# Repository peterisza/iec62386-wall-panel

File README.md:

This is a smart-home wall panel that is intended to be DALI-compatible when it's finished. It has sensors for temperature, humidity, air pressure, and CO2. Its front is customizable and user-swappable with up to 16 capacitive touch channels.

## Status / Important Notice

This project is a **prototype** and **not a consumer product**. It is under active development and may be incomplete, unstable, or non-compliant with relevant standards.

### DO NOT CONNECT TO A REAL DALI NETWORK (YET)

**Do not connect this device to any production / real DALI installation.**  
The current firmware is not DALI-compliant and is intended for development only. In its current state it will:
- transmit debug frames (e.g., 16-bit debug frames),
- respond incorrectly to forward frames (e.g., fixed/placeholder back frame behavior),
- cause unexpected bus behavior.

## Safety / Disclaimer

- Provided **AS IS**, **WITHOUT WARRANTY** of any kind (express or implied).
- You are solely responsible for verifying **electrical safety**, **EMC**, and **regulatory compliance** before any real-world installation or use.
- Not intended for **safety-critical** or life-safety applications (medical, fire protection, emergency systems, etc.).
- If you 3D-print the enclosure, use appropriate **flame-retardant** materials and follow local building and electrical codes.
- By using, building, or distributing this project (or derivatives), you accept that you do so **at your own risk**.

## DALI Compatibility, Certification, and Trademarks

This project is designed with future DALI compatibility in mind, but it is **NOT DALI certified**.

- Certification is performed by the **DALI Alliance / DiiA**. This project is **not certified** and **not affiliated** with the DALI Alliance / DiiA.
- “DALI” and related marks are trademarks of their respective owners. Any mention is for compatibility and informational purposes only.

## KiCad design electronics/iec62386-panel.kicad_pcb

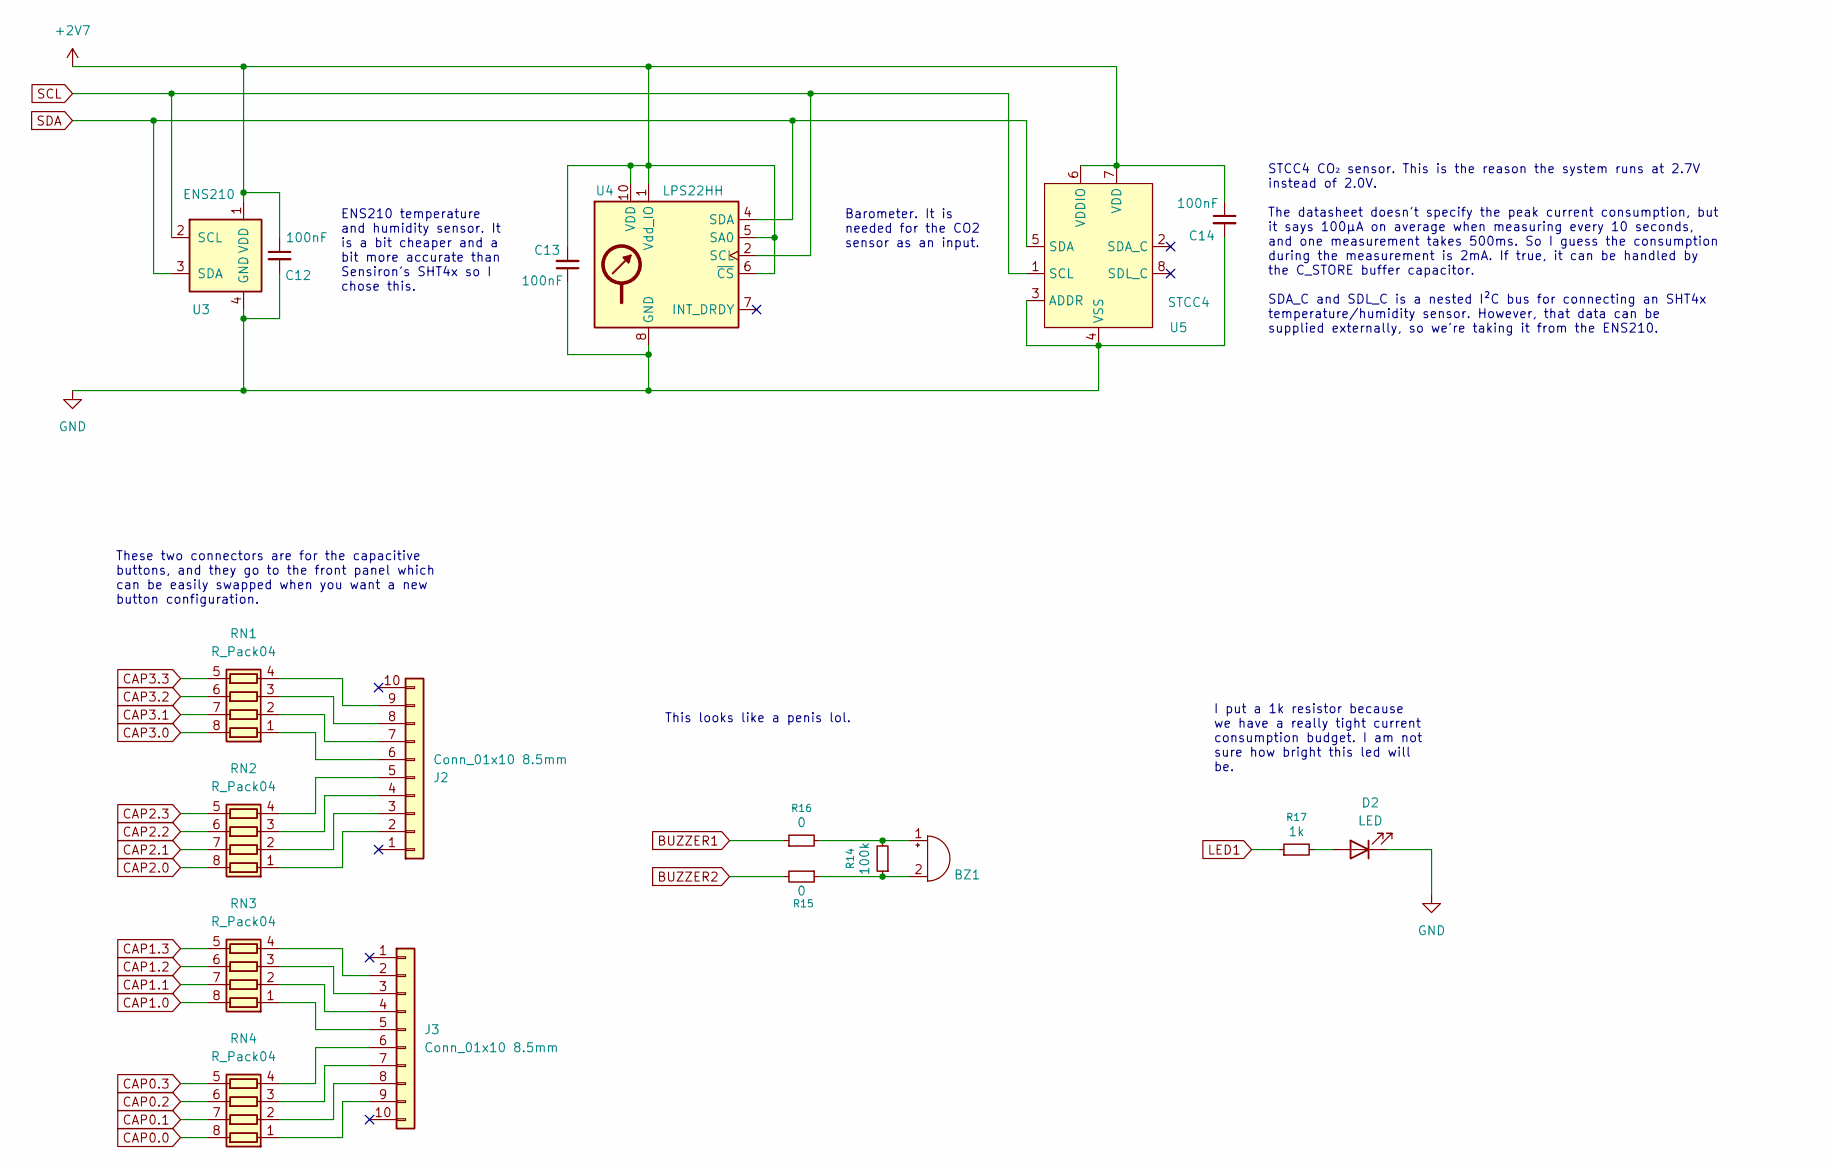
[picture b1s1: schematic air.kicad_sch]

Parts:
BZ1: Buzzer_CUI_CPT-9019S-SMT
C12, C13, C14: 100nF; C_0603_1608Metric_Pad1.08x0.95mm_HandSolder
D2: LED; LED_0603_1608Metric_Pad1.05x0.95mm_HandSolder
J2, J3: Conn_01x10 8.5mm; PinSocket_1x10_P2.54mm_Vertical
R14: 100k; R_0603_1608Metric_Pad0.98x0.95mm_HandSolder
R15, R16: 0; R_0603_1608Metric_Pad0.98x0.95mm_HandSolder
R17: 1k; R_0603_1608Metric_Pad0.98x0.95mm_HandSolder
RN1, RN2, RN3, RN4: R_Pack04; R_Cat16-4-DEBUG
U3: ENS210; AMS_QFN-4-1EP_2x2mm_P0.95mm_EP0.7x1.6mm-DEBUG
U4: LPS22HH; ST_HLGA-10_2x2mm_P0.5mm_LayoutBorder3x2y-DEBUG
U5: STCC4; STCC4-LGA

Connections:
+2V7: C12.1, C13.2, C14.1, U3.1 (VDD), U4.1 (Vdd_IO), U4.5 (SA0), U4.6 (~CS), U4.10 (VDD), U5.6 (VDDIO), U5.7 (VDD); also elsewhere on the board
BUZZER1: R16.1; also elsewhere on the board
BUZZER2: R15.2; also elsewhere on the board
CAP0.0: RN4.8 (R1.2); also elsewhere on the board
CAP0.1: RN4.7 (R2.2); also elsewhere on the board
CAP0.2: RN4.6 (R3.2); also elsewhere on the board
CAP0.3: RN4.5 (R4.2); also elsewhere on the board
CAP1.0: RN3.8 (R1.2); also elsewhere on the board
CAP1.1: RN3.7 (R2.2); also elsewhere on the board
CAP1.2: RN3.6 (R3.2); also elsewhere on the board
CAP1.3: RN3.5 (R4.2); also elsewhere on the board
CAP2.0: RN2.8 (R1.2); also elsewhere on the board
CAP2.1: RN2.7 (R2.2); also elsewhere on the board
CAP2.2: RN2.6 (R3.2); also elsewhere on the board
CAP2.3: RN2.5 (R4.2); also elsewhere on the board
CAP3.0: RN1.8 (R1.2); also elsewhere on the board
CAP3.1: RN1.7 (R2.2); also elsewhere on the board
CAP3.2: RN1.6 (R3.2); also elsewhere on the board
CAP3.3: RN1.5 (R4.2); also elsewhere on the board
GND: C12.2, C13.1, C14.2, D2.1 (K), U3.4 (GND), U3.5 (GND), U4.3 (GND), U4.8 (GND), U4.9 (GND), U5.3 (ADDR), U5.4 (VSS); also elsewhere on the board
LED1: R17.1; also elsewhere on the board
unnamed: BZ1.1 (+), R14.2, R16.2
unnamed: BZ1.2 (-), R14.1, R15.1
unnamed: D2.2 (A), R17.2
unnamed: J2.2, RN2.1 (R1.1)
unnamed: J2.3, RN2.2 (R2.1)
unnamed: J2.4, RN2.3 (R3.1)
unnamed: J2.5, RN2.4 (R4.1)
unnamed: J2.6, RN1.1 (R1.1)
unnamed: J2.7, RN1.2 (R2.1)
unnamed: J2.8, RN1.3 (R3.1)
unnamed: J2.9, RN1.4 (R4.1)
unnamed: J3.2, RN3.4 (R4.1)
unnamed: J3.3, RN3.3 (R3.1)
unnamed: J3.4, RN3.2 (R2.1)
unnamed: J3.5, RN3.1 (R1.1)
unnamed: J3.6, RN4.4 (R4.1)
unnamed: J3.7, RN4.3 (R3.1)
unnamed: J3.8, RN4.2 (R2.1)
unnamed: J3.9, RN4.1 (R1.1)
SCL: U3.2 (SCL), U4.2 (SCL), U5.1 (SCL); also elsewhere on the board
SDA: U3.3 (SDA), U4.4 (SDA), U5.5 (SDA); also elsewhere on the board

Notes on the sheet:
Barometer. It is needed for the CO2 sensor as an input.
STCC4 CO₂ sensor. This is the reason the system runs at 2.7V instead of 2.0V. The datasheet doesn't specify the peak current consumption, but it says 100µA on average when measuring every 10 seconds, and one measurement takes 500ms. So I guess the consumption during the measurement is 2mA. If true,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
ENS210 temperature and humidity sensor. It is a bit cheaper and a bit more accurate than Sensiron's SHT4x so I chose this.
I put a 1k resistor because we have a really tight current consumption budget. I am not sure how bright this led will be.
These two connectors are for the capacitive buttons, and they go to the front panel which can be easily swapped when you want a new button configuration.
This looks like a penis lol.

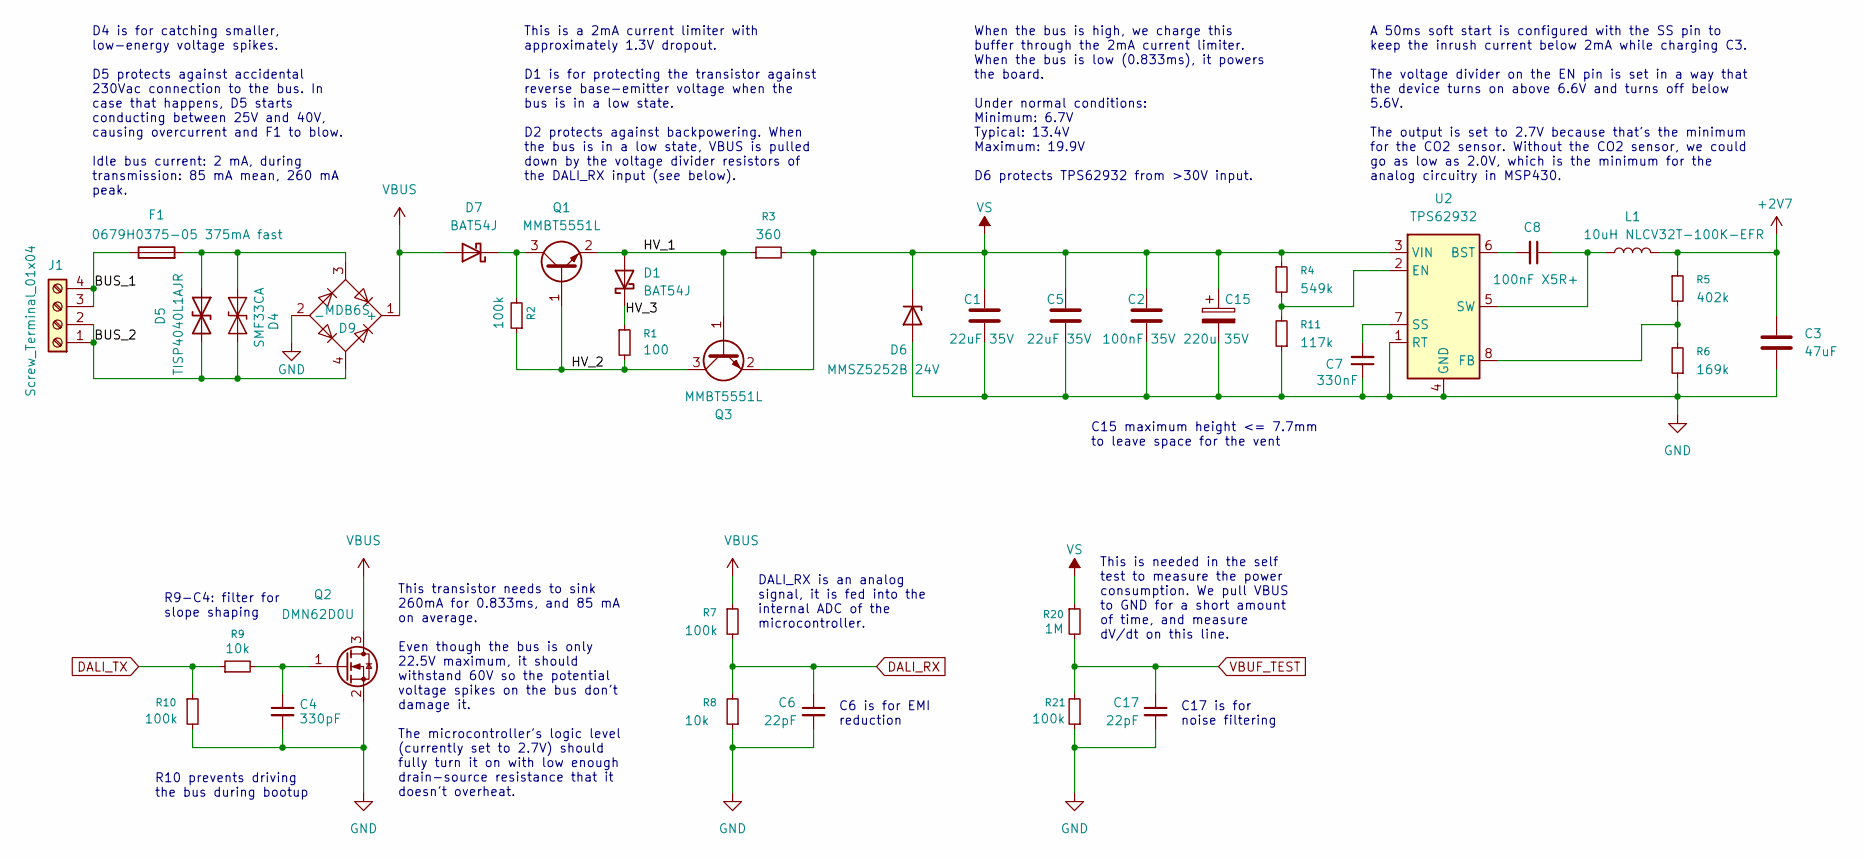
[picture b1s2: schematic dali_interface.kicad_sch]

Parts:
C1, C5: 22uF 35V; C_1206_3216Metric_Pad1.33x1.80mm_HandSolder
C2: 100nF 35V; C_0603_1608Metric_Pad1.08x0.95mm_HandSolder
C3: 47uF; C_0805_2012Metric_Pad1.18x1.45mm_HandSolder
C4: 330pF; C_0603_1608Metric_Pad1.08x0.95mm_HandSolder
C6, C17: 22pF; C_0603_1608Metric_Pad1.08x0.95mm_HandSolder
C7: 330nF; C_0603_1608Metric_Pad1.08x0.95mm_HandSolder
C8: 100nF X5R+; C_0603_1608Metric_Pad1.08x0.95mm_HandSolder
C15: 220u 35V; CP_Elec_6.3x7.7
D1, D7: BAT54J; D_SOD-323_HandSoldering
D4: SMF33CA; D_SOD-123-DEBUG
D5: TISP4040L1AJR; D_SMA
D6: MMSZ5252B 24V; D_SOD-123F
D9: MDB6S; TSSOP-4_4.4x5mm_P4mm
F1: 0679H0375-05 375mA fast; FUSE_0679H_BEL
J1: Screw_Terminal_01x04; TerminalBlock_MetzConnect_Type086_RT03404HBLC_1x04_P3.81mm_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
L1: 10uH NLCV32T-100K-EFR; L_TDK_NLV32_3.2x2.5mm
Q1, Q3: MMBT5551L; SOT-23
Q2: DMN62D0U; SOT-23
R1: 100; R_0603_1608Metric_Pad0.98x0.95mm_HandSolder
R2, R7, R10, R21: 100k; R_0603_1608Metric_Pad0.98x0.95mm_HandSolder
R3: 360; R_0603_1608Metric_Pad0.98x0.95mm_HandSolder
R4: 549k; R_0603_1608Metric_Pad0.98x0.95mm_HandSolder
R5: 402k; R_0603_1608Metric_Pad0.98x0.95mm_HandSolder
R6: 169k; R_0603_1608Metric_Pad0.98x0.95mm_HandSolder
R8, R9: 10k; R_0603_1608Metric_Pad0.98x0.95mm_HandSolder
R11: 117k; R_0603_1608Metric_Pad0.98x0.95mm_HandSolder
R20: 1M; R_0603_1608Metric_Pad0.98x0.95mm_HandSolder
U2: TPS62932; SOT-583-8-DEBUG

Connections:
+2V7: C3.1, L1.2, R5.1; also elsewhere on the board
/IEC 62386 interface/BUS_1: F1.1, J1.3, J1.4
/IEC 62386 interface/BUS_2: D4.1 (A1), D5.2 (A2), D9.4, J1.1, J1.2
/IEC 62386 interface/HV_1: D1.2 (A), Q1.2 (E), Q3.1 (B), R3.1
/IEC 62386 interface/HV_2: Q1.1 (B), Q3.3 (C), R1.2, R2.1
/IEC 62386 interface/HV_3: D1.1 (K), R1.1
DALI_RX: C6.1, R7.2, R8.2; also elsewhere on the board
DALI_TX: R9.1, R10.1; also elsewhere on the board
GND: C1.2, C2.2, C3.2, C4.2, C5.2, C6.2, C7.1, C15.2, C17.2, D6.2 (A), D9.2 (-), Q2.2 (S), R6.1, R8.1, R10.2, R11.1, R21.1, U2.1 (RT), U2.4 (GND); also elsewhere on the board
unnamed: D4.2 (A2), D5.1 (A1), D9.3, F1.2
unnamed: D7.1 (K), Q1.3 (C), R2.2
unnamed: C4.1, Q2.1 (G), R9.2
unnamed: C8.2, U2.6 (BST)
unnamed: R4.2, R11.2, U2.2 (EN)
unnamed: R5.2, R6.2, U2.8 (FB)
unnamed: C7.2, U2.7 (SS)
unnamed: C8.1, L1.1, U2.5 (SW)
VBUF_TEST: C17.1, R20.2, R21.2; also elsewhere on the board
VBUS: D7.2 (A), D9.1 (+), Q2.3 (D), R7.1
VS: C1.1, C2.1, C5.1, C15.1, D6.1 (K), Q3.2 (E), R3.2, R4.1, R20.1, U2.3 (VIN)

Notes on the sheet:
DALI_RX is an analog signal, it is fed into the internal ADC of the microcontroller.
C17 is for noise filtering
C6 is for EMI reduction
C15 maximum height <= 7.7mm to leave space for the vent
This is a 2mA current limiter with approximately 1.3V dropout. D1 is for protecting the transistor against reverse base-emitter voltage when the bus is in a low state. D2 protects against backpowering. When the bus is in a low state, VBUS is pulled down by the voltage divider resistors of the DALI_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
This is needed in the self test to measure the power consumption. We pull VBUS to GND for a short amount of time, and measure dV/dt on this line.
When the bus is high, we charge this buffer through the 2mA current limiter. When the bus is low (0.833ms), it powers the board. Under normal conditions: Minimum: 6.7V Typical: 13.4V Maximum: 19.9V D6 protects TPS62932 from >30V input.
D4 is for catching smaller, low-energy voltage spikes. D5 protects against accidental 230Vac connection to the bus. In case that happens, D5 starts conducting between 25V and 40V, causing overcurrent and F1 to blow. Idle bus current: 2 mA, during transmission: 85 mA mean, 260 mA peak.
R10 prevents driving the bus during bootup
R9-C4: filter for slope shaping
A 50ms soft start is configured with the SS pin to keep the inrush current below 2mA while charging C3. The voltage divider on the EN pin is set in a way that the device turns on above 6.6V and turns off below 5.6V. The output is set to 2.7V because that's the minimum for the CO2 sensor. Without th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
This transistor needs to sink 260mA for 0.833ms, and 85 mA on average. Even though the bus is only 22.5V maximum, it should withstand 60V so the potential voltage spikes on the bus don't damage it. The microcontroller's logic level (currently set to 2.7V) should fully turn it on with low enough dra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

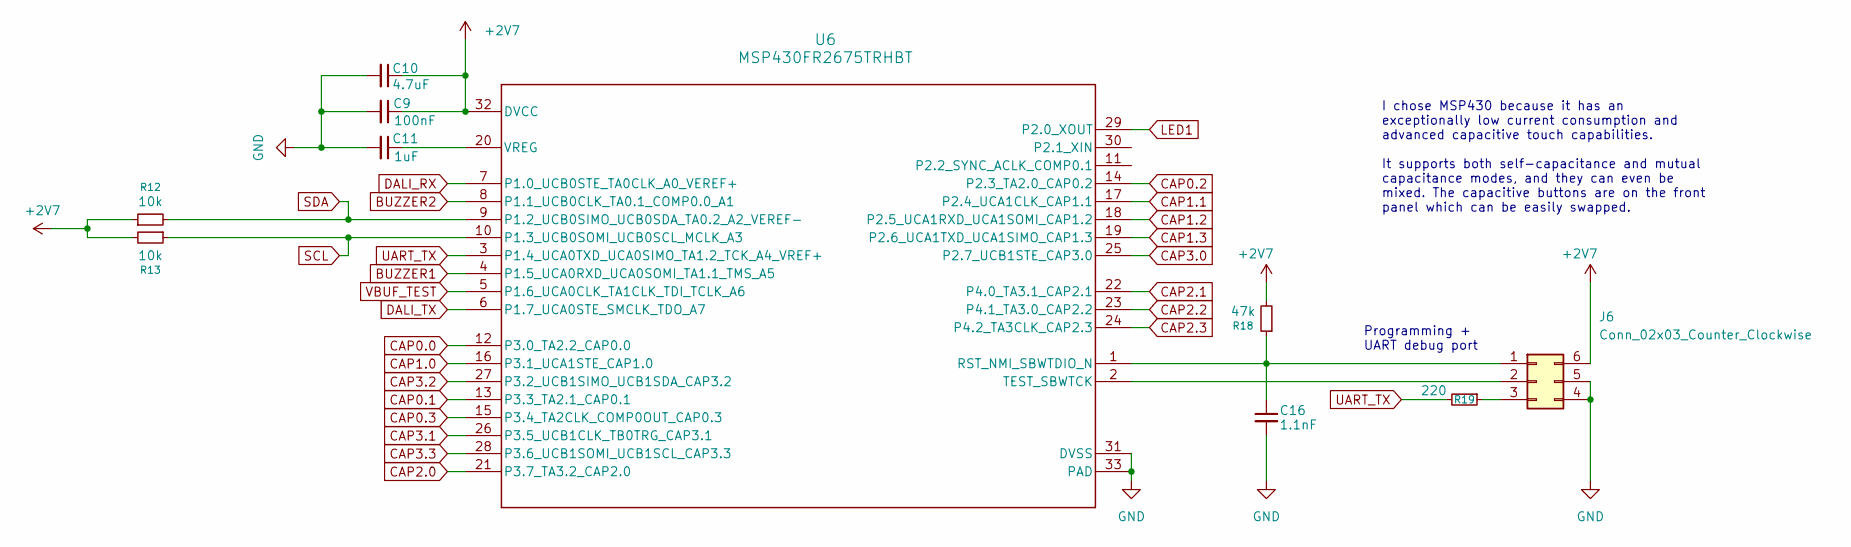
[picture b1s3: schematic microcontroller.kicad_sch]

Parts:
C9: 100nF; C_0603_1608Metric_Pad1.08x0.95mm_HandSolder
C10: 4.7uF; C_0603_1608Metric_Pad1.08x0.95mm_HandSolder
C11: 1uF; C_0603_1608Metric_Pad1.08x0.95mm_HandSolder
C16: 1.1nF; C_0603_1608Metric_Pad1.08x0.95mm_HandSolder
J6: Conn_02x03_Counter_Clockwise; PinSocket_2x03_P1.27mm_Vertical
R12, R13: 10k; R_0603_1608Metric_Pad0.98x0.95mm_HandSolder
R18: 47k; R_0603_1608Metric_Pad0.98x0.95mm_HandSolder
R19: 220; R_0603_1608Metric_Pad0.98x0.95mm_HandSolder
U6: MSP430FR2675TRHBT; QFN-32-1EP_5x5mm_P0.5mm_EP3.1x3.1mm

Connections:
+2V7: C9.1, C10.1, J6.6, R12.1, R13.2, R18.2, U6.32 (DVCC); also elsewhere on the board
BUZZER1: U6.4 (P1.5_UCA0RXD_UCA0SOMI_TA1.1_TMS_A5); also elsewhere on the board
BUZZER2: U6.8 (P1.1_UCB0CLK_TA0.1_COMP0.0_A1); also elsewhere on the board
CAP0.0: U6.12 (P3.0_TA2.2_CAP0.0); also elsewhere on the board
CAP0.1: U6.13 (P3.3_TA2.1_CAP0.1); also elsewhere on the board
CAP0.2: U6.14 (P2.3_TA2.0_CAP0.2); also elsewhere on the board
CAP0.3: U6.15 (P3.4_TA2CLK_COMP0OUT_CAP0.3); also elsewhere on the board
CAP1.0: U6.16 (P3.1_UCA1STE_CAP1.0); also elsewhere on the board
CAP1.1: U6.17 (P2.4_UCA1CLK_CAP1.1); also elsewhere on the board
CAP1.2: U6.18 (P2.5_UCA1RXD_UCA1SOMI_CAP1.2); also elsewhere on the board
CAP1.3: U6.19 (P2.6_UCA1TXD_UCA1SIMO_CAP1.3); also elsewhere on the board
CAP2.0: U6.21 (P3.7_TA3.2_CAP2.0); also elsewhere on the board
CAP2.1: U6.22 (P4.0_TA3.1_CAP2.1); also elsewhere on the board
CAP2.2: U6.23 (P4.1_TA3.0_CAP2.2); also elsewhere on the board
CAP2.3: U6.24 (P4.2_TA3CLK_CAP2.3); also elsewhere on the board
CAP3.0: U6.25 (P2.7_UCB1STE_CAP3.0); also elsewhere on the board
CAP3.1: U6.26 (P3.5_UCB1CLK_TB0TRG_CAP3.1); also elsewhere on the board
CAP3.2: U6.27 (P3.2_UCB1SIMO_UCB1SDA_CAP3.2); also elsewhere on the board
CAP3.3: U6.28 (P3.6_UCB1SOMI_UCB1SCL_CAP3.3); also elsewhere on the board
DALI_RX: U6.7 (P1.0_UCB0STE_TA0CLK_A0_VEREF+); also elsewhere on the board
DALI_TX: U6.6 (P1.7_UCA0STE_SMCLK_TDO_A7); also elsewhere on the board
GND: C9.2, C10.2, C11.2, C16.2, J6.4, J6.5, U6.31 (DVSS), U6.33 (PAD); also elsewhere on the board
LED1: U6.29 (P2.0_XOUT); also elsewhere on the board
unnamed: C16.1, J6.1, R18.1, U6.1 (RST_NMI_SBWTDIO_N)
unnamed: J6.2, U6.2 (TEST_SBWTCK)
unnamed: J6.3, R19.1
unnamed: C11.1, U6.20 (VREG)
SCL: R13.1, U6.10 (P1.3_UCB0SOMI_UCB0SCL_MCLK_A3); also elsewhere on the board
SDA: R12.2, U6.9 (P1.2_UCB0SIMO_UCB0SDA_TA0.2_A2_VEREF-); also elsewhere on the board
UART_TX: R19.2, U6.3 (P1.4_UCA0TXD_UCA0SIMO_TA1.2_TCK_A4_VREF+)
VBUF_TEST: U6.5 (P1.6_UCA0CLK_TA1CLK_TDI_TCLK_A6); also elsewhere on the board

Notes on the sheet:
I chose MSP430 because it has an exceptionally low current consumption and advanced capacitive touch capabilities. It supports both self-capacitance and mutual capacitance modes, and they can even be mixed. The capacitive buttons are on the front panel which can be easily swapped.
Programming + UART debug port

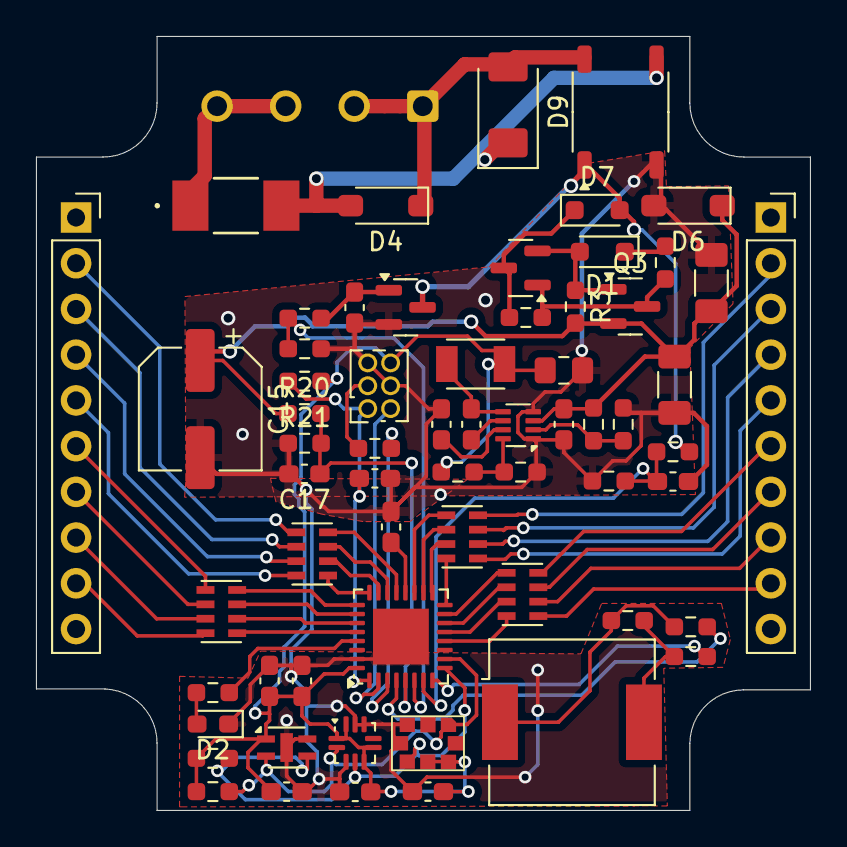
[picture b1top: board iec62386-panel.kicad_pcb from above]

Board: 2 copper layers, 43.0 x 43.0 mm, 64 parts (1 on the bottom side), 65 nets.

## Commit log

2025-10-16 Initial commit of the HW
2025-10-20 Trying to get the mcu running
2025-10-21 Plastic frame and enclosure
2025-10-21 Added mouse ears, fixed connector hole sizes, decreased box height
2025-10-24 Got the touch panel to do something, modified the enclosure a little bit
2025-11-05 Added wall standoff to frame, refactored openscad code, added clay mold test model
2025-11-05 Refactored the firmware Now the sensors and the touch sensor work simultaneously
2025-11-25 todo + debugging weird analog glitches, trying to make the firmware work
    dali initial test code
2025-11-27 finally able to receive and decode dali forward frames and respond to them with a backward frame
2025-12-02 Fixed errors of the first hw prototype
2025-12-02 front panel test pcb
2025-12-07 now everything works: reading sensor data, capacitive touch, receiving and sending DALI frames
    most of DALI isn't implemented still
2025-12-07 a bit of refactoring + fixed the clock frequency for captivate
2025-12-07 added random number generator, added DALI tx buffer
2025-12-09 added DALI collision handling, removed collision handling from backward frames
2025-12-10 Now using ADC interrupt instead of timer interrupt for DALI, fixed obvious error in collision handling
2025-12-12 test scripts for the hasseb USB DALI master
2025-12-18 added temporary 16-bit broadcast messages for debugging, added node.js hasseb bus sniffer
2025-12-28 added 16 bit broadcast test messages for debugging
2025-12-28 Add files via upload
    license
2025-12-28 Licenses
